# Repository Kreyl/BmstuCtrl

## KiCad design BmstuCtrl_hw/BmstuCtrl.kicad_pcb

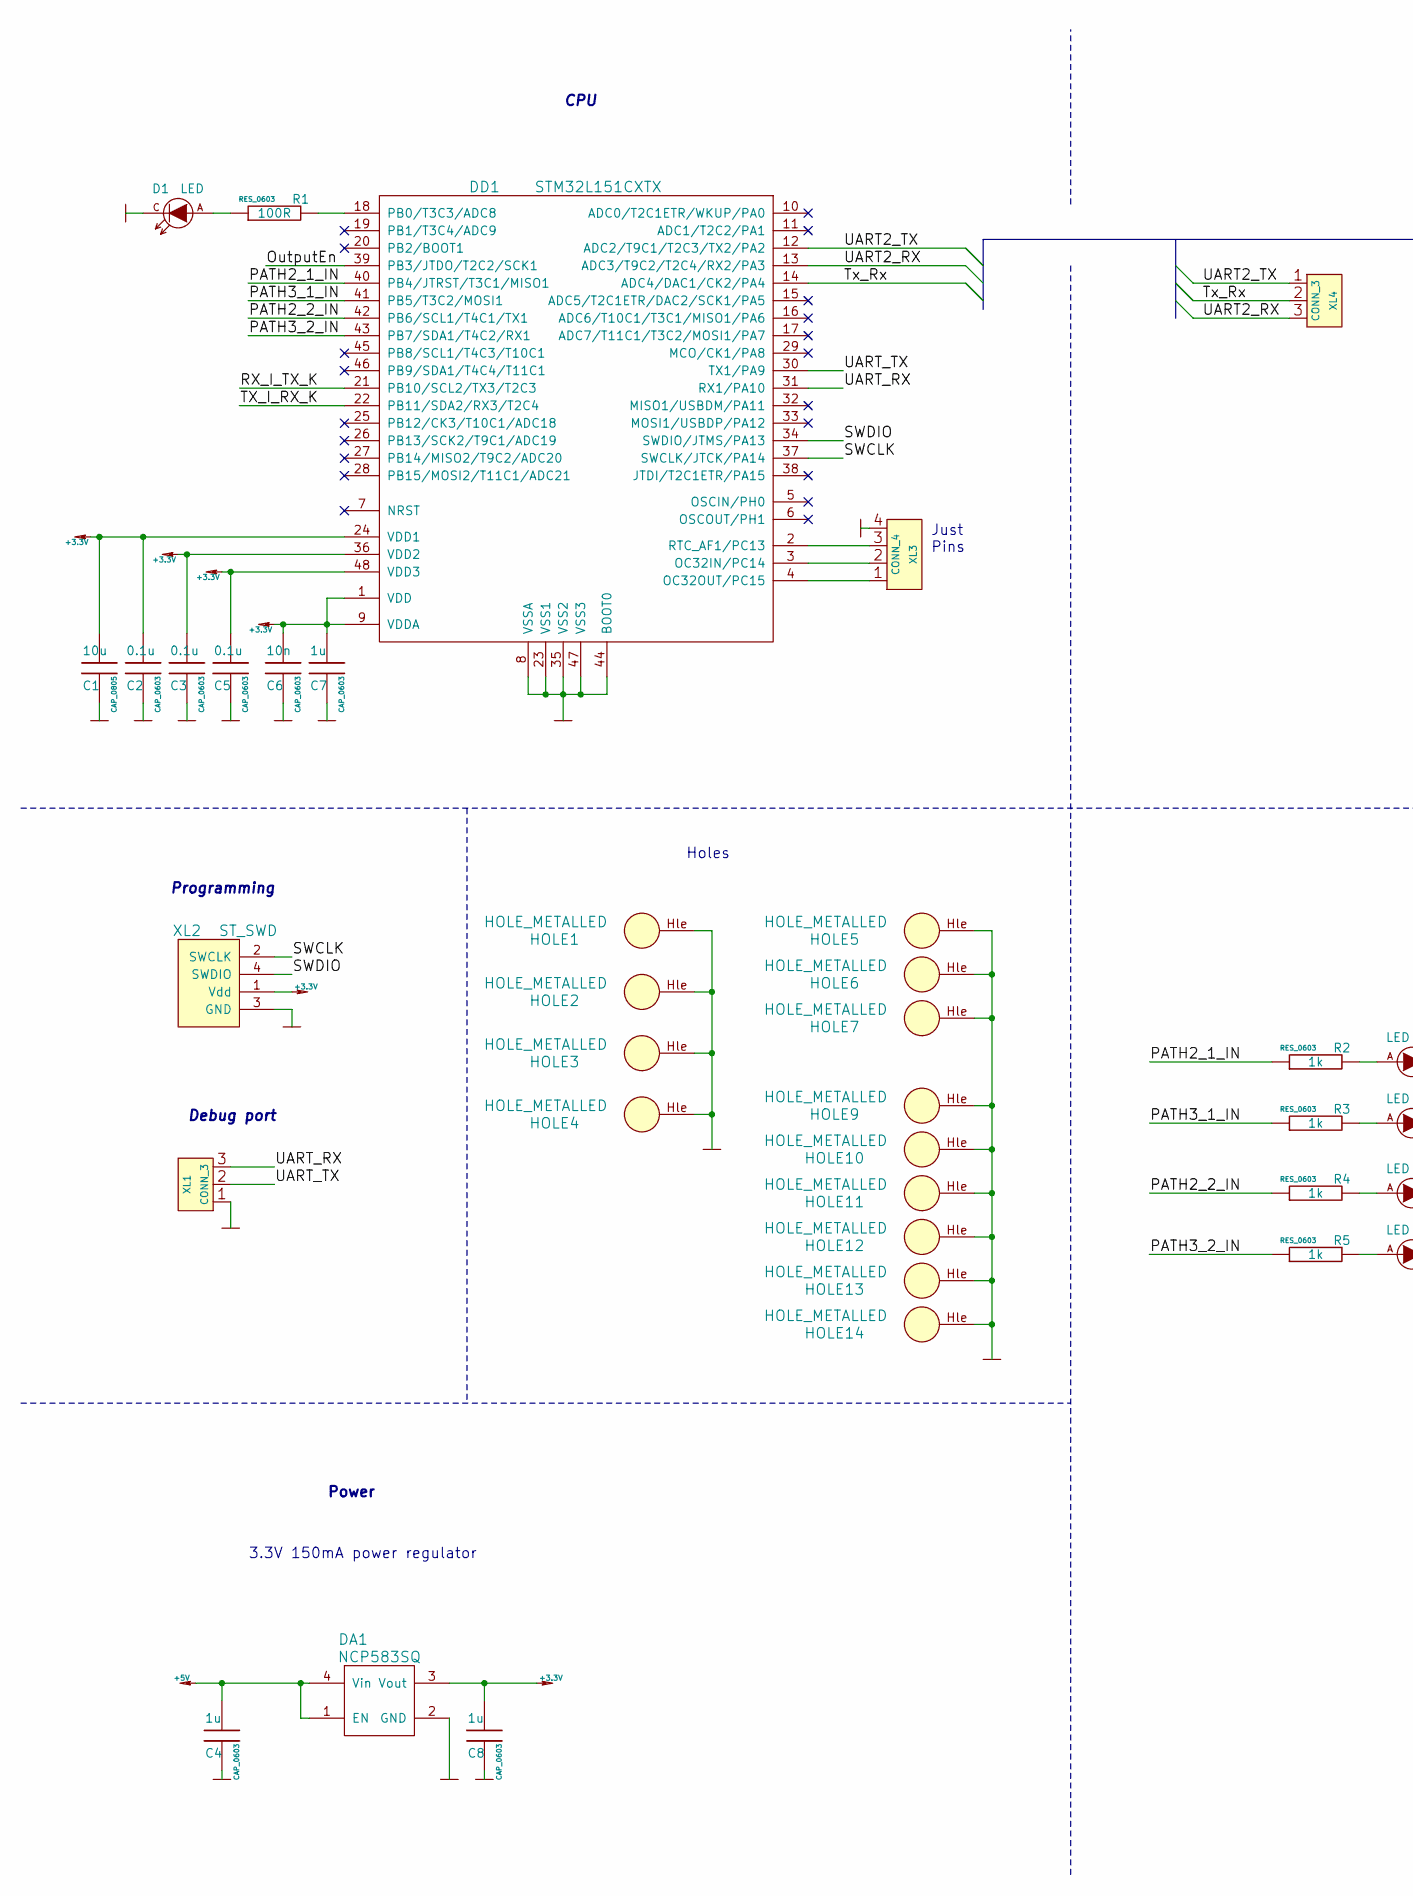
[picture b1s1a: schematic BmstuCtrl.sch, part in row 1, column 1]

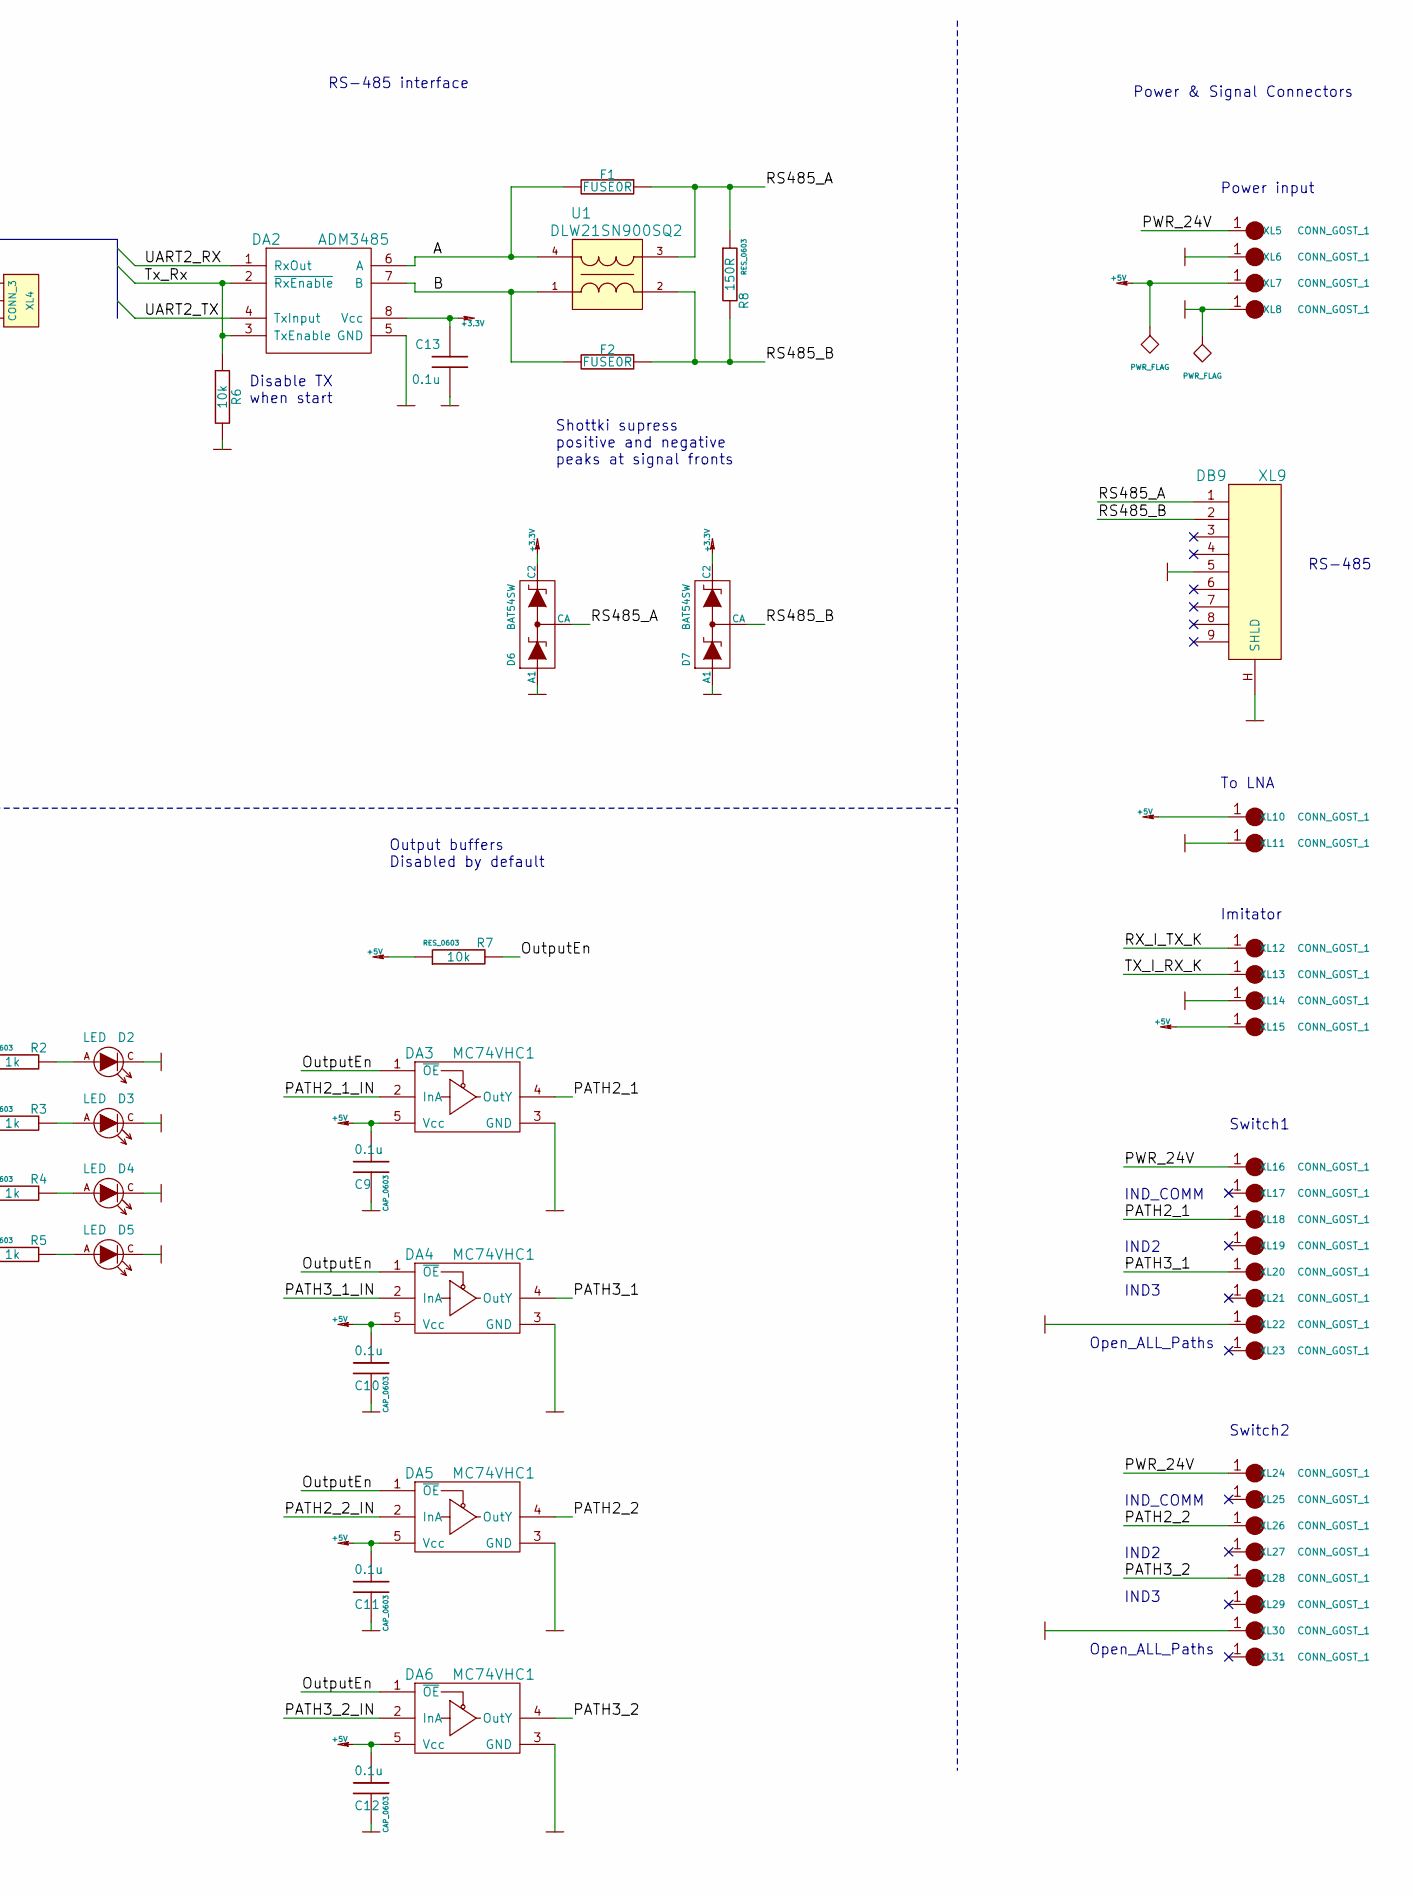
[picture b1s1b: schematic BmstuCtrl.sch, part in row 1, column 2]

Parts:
C1: 10u; CAP_0805
C2, C3, C5, C9, C10, C11, C12: 0.1u; CAP_0603
C4, C7, C8: 1u; CAP_0603
C6: 10n; CAP_0603
C13: 0.1u
D1, D2, D3, D4, D5: LED
D6, D7: BAT54SW
DA1: NCP583SQ
DA2: ADM3485
DA3, DA4, DA5, DA6: MC74VHC1
DD1: STM32L151CXTX
F1, F2: FUSE0R
HOLE1, HOLE2, HOLE3, HOLE4, HOLE5, HOLE6, HOLE7, HOLE9, HOLE10, HOLE11, HOLE12, HOLE13, HOLE14: HOLE_METALLED
R1: 100R; RES_0603
R2, R3, R4, R5: 1k; RES_0603
R6: 10k
R7: 10k; RES_0603
R8: 150R; RES_0603
U1: DLW21SN900SQ2
XL1: CONN_3
XL2: ST_SWD
XL3: CONN_4
XL4: CONN_3
XL5, XL6, XL7, XL8, XL10, XL11, XL12, XL13, XL14, XL15, XL16, XL17, XL18, XL19, XL20, XL21, XL22, XL23, XL24, XL25, XL26, XL27, XL28, XL29, XL30, XL31: CONN_GOST_1
XL9: DB9

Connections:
+3.3V: C1.1, C2.1, C3.1, C5.1, C6.1, C7.1, C8.1, C13.1, D6.2 (C2), D7.2 (C2), DA1.3 (Vout), DA2.8 (Vcc), DD1.1 (VDD), DD1.9 (VDDA), DD1.24 (VDD1), DD1.36 (VDD2), DD1.48 (VDD3), XL2.1 (Vdd)
+5V: C4.1, C9.1, C10.1, C11.1, C12.1, DA1.1 (EN), DA1.4 (Vin), DA3.5 (Vcc), DA4.5 (Vcc), DA5.5 (Vcc), DA6.5 (Vcc), R7.1, XL7.1, XL10.1, XL15.1
/A: DA2.6 (A), F1.2, U1.4
/B: DA2.7 (B), F2.2, U1.1
/OutputEn: DA3.1 (~OE), DA4.1 (~OE), DA5.1 (~OE), DA6.1 (~OE), DD1.39 (PB3/JTDO/T2C2/SCK1), R7.2
/PATH2_1: DA3.4 (OutY), XL18.1
/PATH2_1_IN: DA3.2 (InA), DD1.40 (PB4/JTRST/T3C1/MISO1), R2.1
/PATH2_2: DA5.4 (OutY), XL26.1
/PATH2_2_IN: DA5.2 (InA), DD1.42 (PB6/SCL1/T4C1/TX1), R4.1
/PATH3_1: DA4.4 (OutY), XL20.1
/PATH3_1_IN: DA4.2 (InA), DD1.41 (PB5/T3C2/MOSI1), R3.1
/PATH3_2: DA6.4 (OutY), XL28.1
/PATH3_2_IN: DA6.2 (InA), DD1.43 (PB7/SDA1/T4C2/RX1), R5.1
/PWR_24V: XL5.1, XL16.1, XL24.1
/RS485_A: D6.3 (CA), F1.1, R8.1, U1.3, XL9.1
/RS485_B: D7.3 (CA), F2.1, R8.2, U1.2, XL9.2
/RX_I_TX_K: DD1.21 (PB10/SCL2/TX3/T2C3), XL12.1
/SWCLK: DD1.37 (SWCLK/JTCK/PA14), XL2.2 (SWCLK)
/SWDIO: DD1.34 (SWDIO/JTMS/PA13), XL2.4 (SWDIO)
/TX_I_RX_K: DD1.22 (PB11/SDA2/RX3/T2C4), XL13.1
/Tx_Rx: DA2.2 (~RxEnable), DA2.3 (TxEnable), DD1.14 (ADC4/DAC1/CK2/PA4), R6.1, XL4.2 (PM)
/UART2_RX: DA2.1 (RxOut), DD1.13 (ADC3/T9C2/T2C4/RX2/PA3), XL4.3
/UART2_TX: DA2.4 (TxInput), DD1.12 (ADC2/T9C1/T2C3/TX2/PA2), XL4.1
/UART_RX: DD1.31 (RX1/PA10), XL1.3
/UART_TX: DD1.30 (TX1/PA9), XL1.2 (PM)
GND: C1.2, C2.2, C3.2, C4.2, C5.2, C6.2, C7.2, C8.2, C9.2, C10.2, C11.2, C12.2, C13.2, D1.C, D2.C, D3.C, D4.C, D5.C, D6.1 (A1), D7.1 (A1), DA1.2 (GND), DA2.5 (GND), DA3.3 (GND), DA4.3 (GND), DA5.3 (GND), DA6.3 (GND), DD1.8 (VSSA), DD1.23 (VSS1), DD1.35 (VSS2), DD1.44 (BOOT0), DD1.47 (VSS3), HOLE1.Hle, HOLE2.Hle, HOLE3.Hle, HOLE4.Hle, HOLE5.Hle, HOLE6.Hle, HOLE7.Hle, HOLE9.Hle, HOLE10.Hle, HOLE11.Hle, HOLE12.Hle, HOLE13.Hle, HOLE14.Hle, R6.2, XL1.1, XL2.3 (GND), XL3.4, XL6.1, XL8.1, XL9.5, XL9.H (SHLD), XL11.1, XL14.1, XL22.1, XL30.1
unnamed: DD1.2 (RTC_AF1/PC13), XL3.3
unnamed: DD1.3 (OC32IN/PC14), XL3.2 (PM)
unnamed: DD1.4 (OC32OUT/PC15), XL3.1
unnamed: DD1.18 (PB0/T3C3/ADC8), R1.2
unnamed: D1.A, R1.1
unnamed: D4.A, R4.2
unnamed: D3.A, R3.2
unnamed: D5.A, R5.2
unnamed: D2.A, R2.2

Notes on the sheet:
Debug port
Programming
CPU
Power
Just Pins
3.3V 150mA power regulator
Shottki supress positive and negative peaks at signal fronts
Disable TX when start
RS-485
Imitator
Power input
To LNA
IND_COMM
IND2
IND3
Open_ALL_Paths
Switch1
Switch2
Output buffers Disabled by default
Holes
RS-485 interface
Power & Signal Connectors

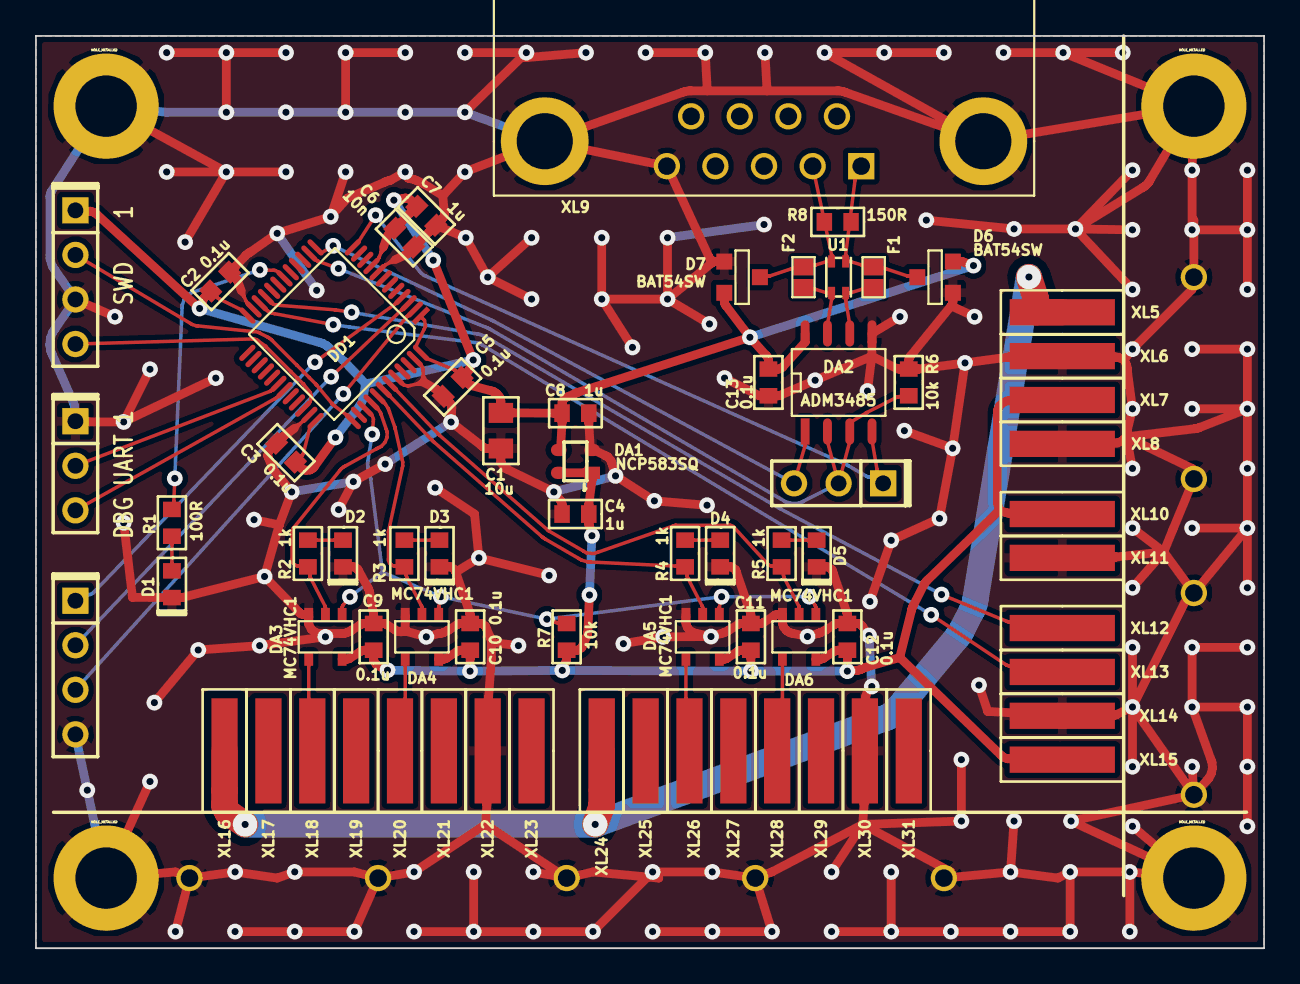
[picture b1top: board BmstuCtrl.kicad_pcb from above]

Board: 2 copper layers, 70.0 x 52.0 mm, 82 parts (0 on the bottom side), 35 nets.

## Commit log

2015-09-28 + Imitator's UART TX & RX Not tested.
2015-09-28 + Current build
2015-09-30 + ACK after Send2Imitator Cmd
2015-09-30 + CurrentBuild
2015-09-30 \n removed
2015-10-09 + protocol.doc
2015-10-09 Добавил бинарный протокол взимодействия контроллера с компом
2015-10-12 Добавил про LSB для CRC
2015-10-17 Пример программы на ПК, формирмирующий пакеты к контроллеру или имитатору.
2015-10-17 no message
